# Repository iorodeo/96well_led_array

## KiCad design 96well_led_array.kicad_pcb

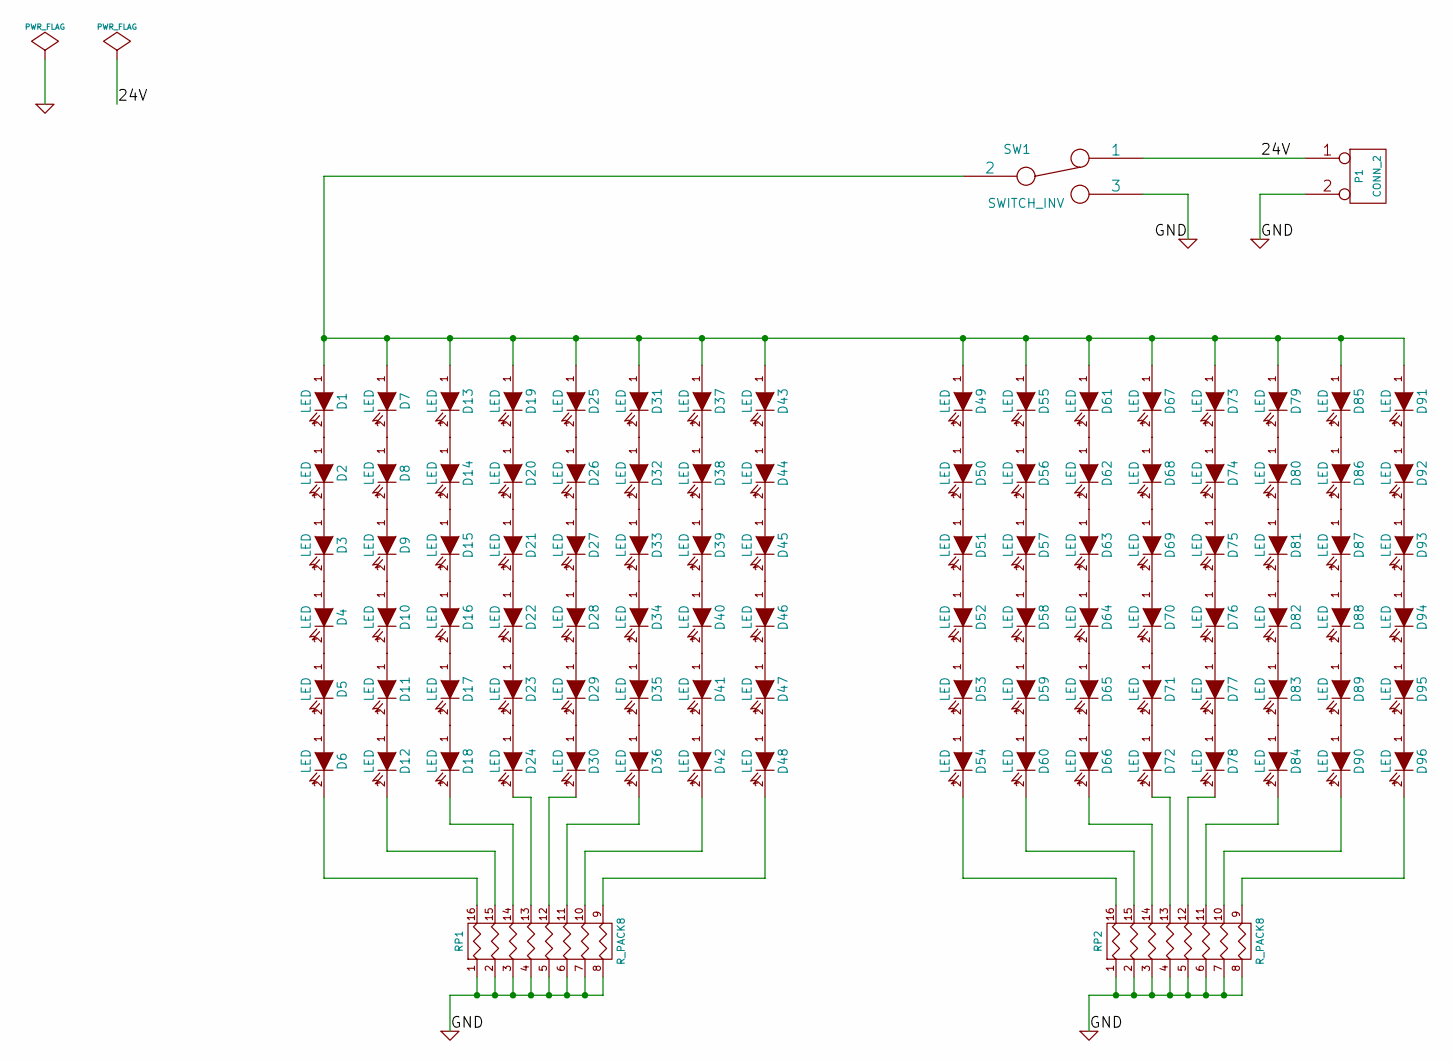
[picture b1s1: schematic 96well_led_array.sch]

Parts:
D1, D2, D3, D4, D5, D6, D7, D8, D9, D10, D11, D12, D13, D14, D15, D16, D17, D18, D19, D20, D21, D22, D23, D24, D25, D26, D27, D28, D29, D30, D31, D32, D33, D34, D35, D36, D37, D38, D39, D40, D41, D42, D43, D44, D45, D46, D47, D48, D49, D50, D51, D52, D53, D54, D55, D56, D57, D58, D59, D60, D61, D62, D63, D64, D65, D66, D67, D68, D69, D70, D71, D72, D73, D74, D75, D76, D77, D78, D79, D80, D81, D82, D83, D84, D85, D86, D87, D88, D89, D90, D91, D92, D93, D94, D95, D96: LED
P1: CONN_2
RP1, RP2: R_PACK8
SW1: SWITCH_INV

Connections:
/24V: P1.1, SW1.1
GND: P1.2 (PM), RP1.1, RP1.2, RP1.3, RP1.4, RP1.5, RP1.6, RP1.7, RP1.8, RP2.1, RP2.2, RP2.3, RP2.4, RP2.5, RP2.6, RP2.7, RP2.8, SW1.3
unnamed: D1.1 (A), D7.1 (A), D13.1 (A), D19.1 (A), D25.1 (A), D31.1 (A), D37.1 (A), D43.1 (A), D49.1 (A), D55.1 (A), D61.1 (A), D67.1 (A), D73.1 (A), D79.1 (A), D85.1 (A), D91.1 (A), SW1.2
unnamed: D36.2 (K), RP1.11 (R6)
unnamed: D18.2 (K), RP1.14 (R3)
unnamed: D30.2 (K), RP1.12 (R5)
unnamed: D24.2 (K), RP1.13 (R4)
unnamed: D96.2 (K), RP2.9 (R8)
unnamed: D95.2 (K), D96.1 (A)
unnamed: D94.2 (K), D95.1 (A)
unnamed: D93.2 (K), D94.1 (A)
unnamed: D92.2 (K), D93.1 (A)
unnamed: D72.2 (K), RP2.13 (R4)
unnamed: D78.2 (K), RP2.12 (R5)
unnamed: D54.2 (K), RP2.16 (R1)
unnamed: D48.2 (K), RP1.9 (R8)
unnamed: D6.2 (K), RP1.16 (R1)
unnamed: D42.2 (K), RP1.10 (R7)
unnamed: D12.2 (K), RP1.15 (R2)
unnamed: D66.2 (K), RP2.14 (R3)
unnamed: D90.2 (K), RP2.10 (R7)
unnamed: D60.2 (K), RP2.15 (R2)
unnamed: D84.2 (K), RP2.11 (R6)
unnamed: D91.2 (K), D92.1 (A)
unnamed: D28.2 (K), D29.1 (A)
unnamed: D34.2 (K), D35.1 (A)
unnamed: D33.2 (K), D34.1 (A)
unnamed: D32.2 (K), D33.1 (A)
unnamed: D31.2 (K), D32.1 (A)
unnamed: D29.2 (K), D30.1 (A)
unnamed: D27.2 (K), D28.1 (A)
unnamed: D26.2 (K), D27.1 (A)
unnamed: D25.2 (K), D26.1 (A)
unnamed: D23.2 (K), D24.1 (A)
unnamed: D40.2 (K), D41.1 (A)
unnamed: D45.2 (K), D46.1 (A)
unnamed: D44.2 (K), D45.1 (A)
unnamed: D43.2 (K), D44.1 (A)
unnamed: D41.2 (K), D42.1 (A)
unnamed: D39.2 (K), D40.1 (A)
unnamed: D38.2 (K), D39.1 (A)
unnamed: D37.2 (K), D38.1 (A)
unnamed: D35.2 (K), D36.1 (A)
unnamed: D11.2 (K), D12.1 (A)
unnamed: D10.2 (K), D11.1 (A)
unnamed: D9.2 (K), D10.1 (A)
unnamed: D8.2 (K), D9.1 (A)
unnamed: D7.2 (K), D8.1 (A)
unnamed: D5.2 (K), D6.1 (A)
unnamed: D4.2 (K), D5.1 (A)
unnamed: D3.2 (K), D4.1 (A)
unnamed: D2.2 (K), D3.1 (A)
unnamed: D1.2 (K), D2.1 (A)
unnamed: D17.2 (K), D18.1 (A)
unnamed: D22.2 (K), D23.1 (A)
unnamed: D21.2 (K), D22.1 (A)
unnamed: D20.2 (K), D21.1 (A)
unnamed: D19.2 (K), D20.1 (A)
unnamed: D46.2 (K), D47.1 (A)
unnamed: D16.2 (K), D17.1 (A)
unnamed: D15.2 (K), D16.1 (A)
unnamed: D14.2 (K), D15.1 (A)
unnamed: D13.2 (K), D14.1 (A)
unnamed: D74.2 (K), D75.1 (A)
unnamed: D79.2 (K), D80.1 (A)
unnamed: D77.2 (K), D78.1 (A)
unnamed: D76.2 (K), D77.1 (A)
unnamed: D75.2 (K), D76.1 (A)
unnamed: D80.2 (K), D81.1 (A)
unnamed: D73.2 (K), D74.1 (A)
unnamed: D71.2 (K), D72.1 (A)
unnamed: D70.2 (K), D71.1 (A)
unnamed: D69.2 (K), D70.1 (A)
unnamed: D85.2 (K), D86.1 (A)
unnamed: D89.2 (K), D90.1 (A)
unnamed: D88.2 (K), D89.1 (A)
unnamed: D87.2 (K), D88.1 (A)
unnamed: D86.2 (K), D87.1 (A)
unnamed: D68.2 (K), D69.1 (A)
unnamed: D83.2 (K), D84.1 (A)
unnamed: D82.2 (K), D83.1 (A)
unnamed: D81.2 (K), D82.1 (A)
unnamed: D51.2 (K), D52.1 (A)
unnamed: D57.2 (K), D58.1 (A)
unnamed: D56.2 (K), D57.1 (A)
unnamed: D55.2 (K), D56.1 (A)
unnamed: D53.2 (K), D54.1 (A)
unnamed: D52.2 (K), D53.1 (A)
unnamed: D50.2 (K), D51.1 (A)
unnamed: D49.2 (K), D50.1 (A)
unnamed: D47.2 (K), D48.1 (A)
unnamed: D63.2 (K), D64.1 (A)
unnamed: D67.2 (K), D68.1 (A)
unnamed: D65.2 (K), D66.1 (A)
unnamed: D64.2 (K), D65.1 (A)
unnamed: D62.2 (K), D63.1 (A)
unnamed: D61.2 (K), D62.1 (A)
unnamed: D59.2 (K), D60.1 (A)
unnamed: D58.2 (K), D59.1 (A)

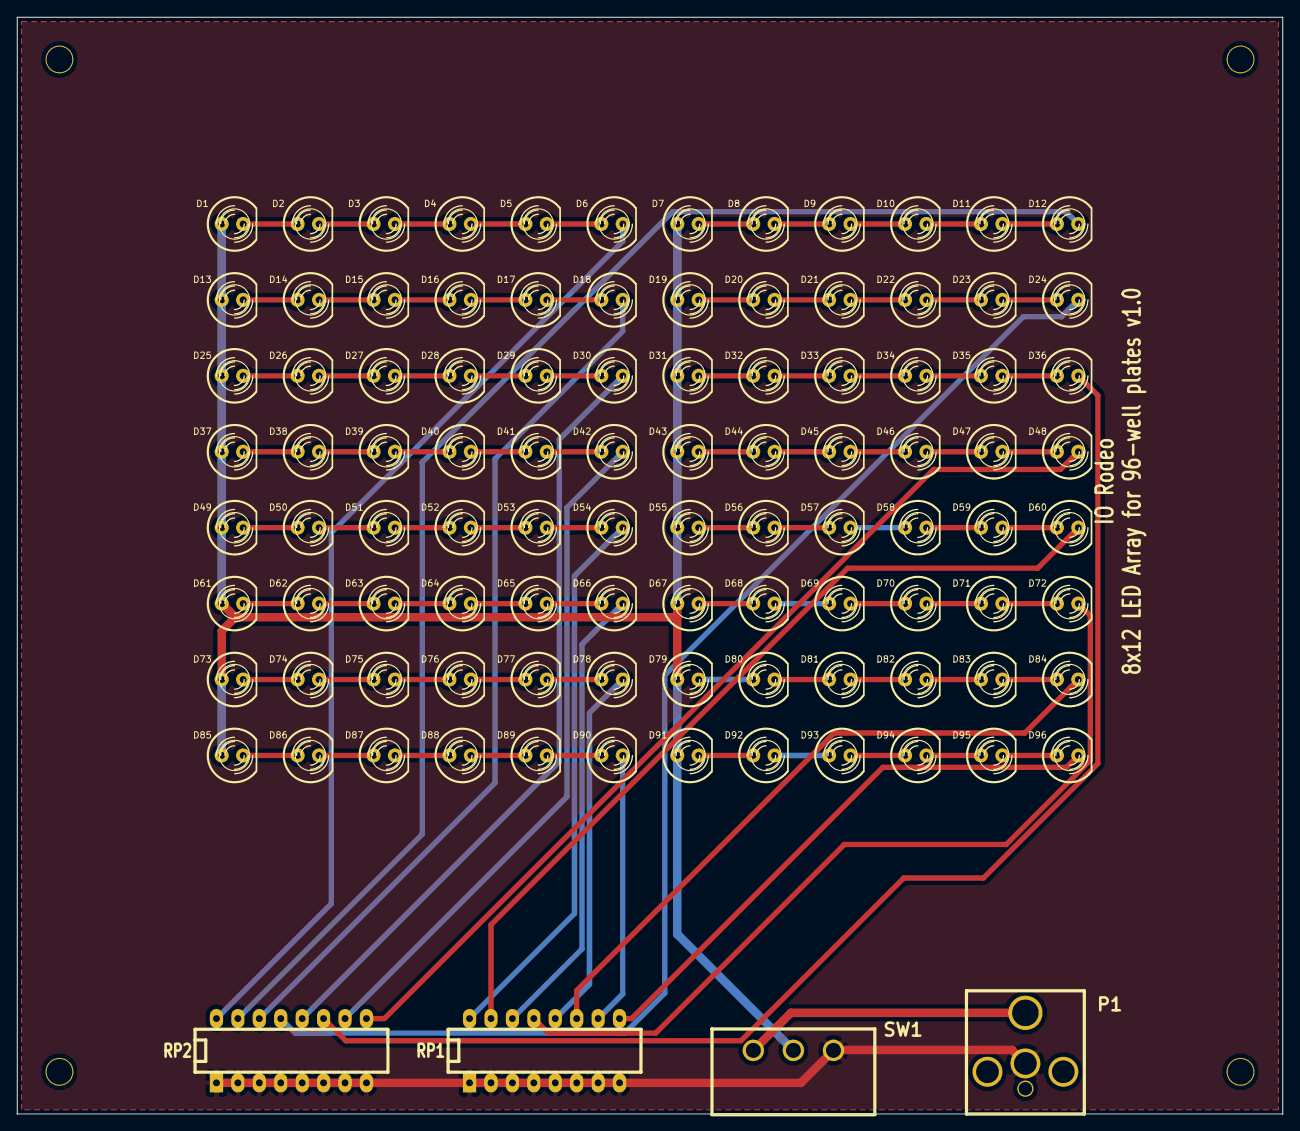
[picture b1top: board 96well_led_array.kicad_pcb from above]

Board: 2 copper layers, 150.0 x 130.0 mm, 104 parts (0 on the bottom side), 99 nets.

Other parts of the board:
M1: 1; MOUNT_HOLE_4_40_GND
M2: 2; MOUNT_HOLE_4_40_GND
M3, M4: VAL**; MOUNT_HOLE_4_40_GND

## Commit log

2014-11-28 Project creation.
